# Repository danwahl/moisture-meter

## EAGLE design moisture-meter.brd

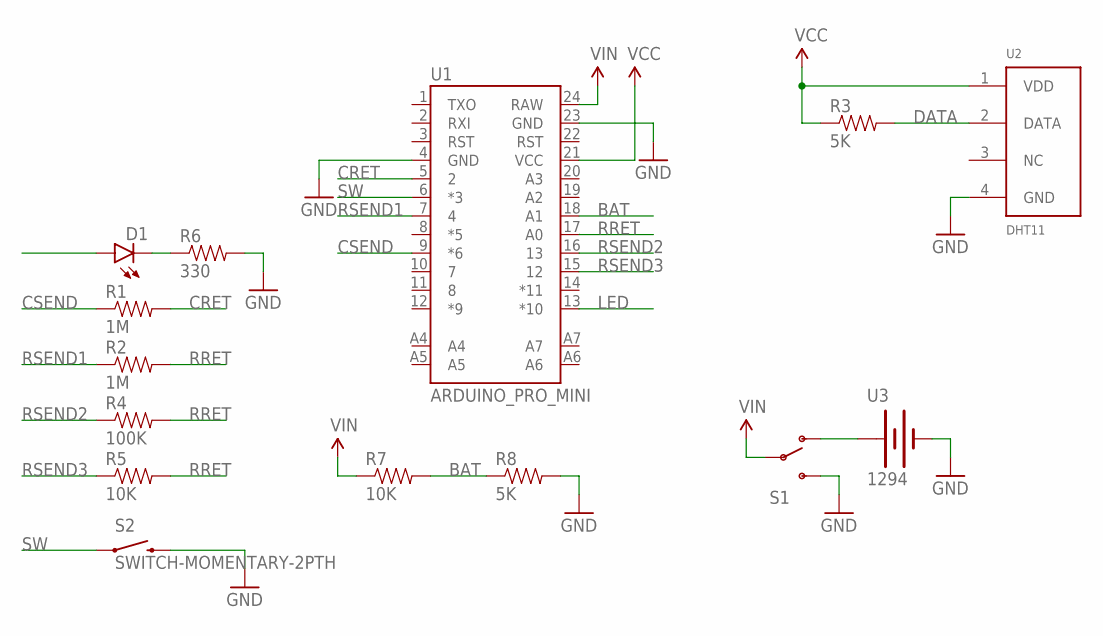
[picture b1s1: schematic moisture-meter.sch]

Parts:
D1: LED5MM
R1, R2: 1M; AXIAL-0.4
R3, R8: 5K; AXIAL-0.4
R4: 100K; AXIAL-0.4
R5, R7: 10K; AXIAL-0.4
R6: 330; AXIAL-0.4
S1: SWITCH-SPDTPTH; SWITCH-SPDT
S2: SWITCH-MOMENTARY-2PTH; TACTILE-PTH
U1: ARDUINO_PRO_MINI
U2: DHT11
U3: 1294

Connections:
BAT: R7.P$2 (2), R8.P$1 (1), U1.18 (A1)
CRET: R1.P$2 (2), U1.5 (2)
CSEND: R1.P$1 (1), U1.9 (*6)
DATA: R3.P$2 (2), U2.2 (DATA)
GND: R6.P$2 (2), R8.P$2 (2), S1.3 (S), S2.3 (2), U1.4 (GND), U1.23 (GND), U2.4 (GND), U3.-
LED: D1.A, U1.13 (*10)
unnamed: D1.K (C), R6.P$1 (1)
unnamed: S1.1 (O), U3.+
RRET: R2.P$2 (2), R4.P$2 (2), R5.P$2 (2), U1.17 (A0)
RSEND1: R2.P$1 (1), U1.7 (4)
RSEND2: R4.P$1 (1), U1.16 (13)
RSEND3: R5.P$1 (1), U1.15 (12)
SW: S2.1, U1.6 (*3)
VCC: R3.P$1 (1), U1.21 (VCC), U2.1 (VDD)
VIN: R7.P$1 (1), S1.2, U1.24 (RAW)

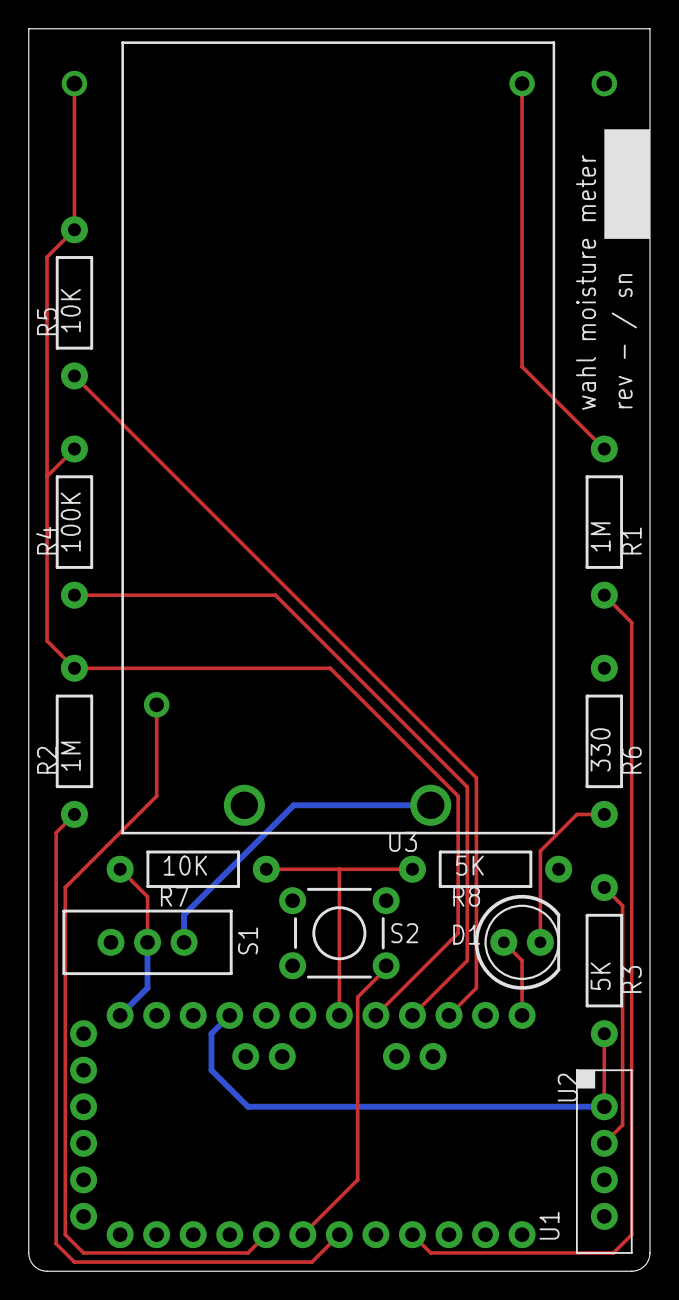
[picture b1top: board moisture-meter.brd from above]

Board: 2 copper layers, 43.2 x 86.4 mm, 14 parts (0 on the bottom side), 15 nets.

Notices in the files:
parts and their libraries:
SparkFun-Resistors: Licensing: Creative Commons ShareAlike 4.0 International - https://creativecommons.org/licenses/by-sa/4.0
